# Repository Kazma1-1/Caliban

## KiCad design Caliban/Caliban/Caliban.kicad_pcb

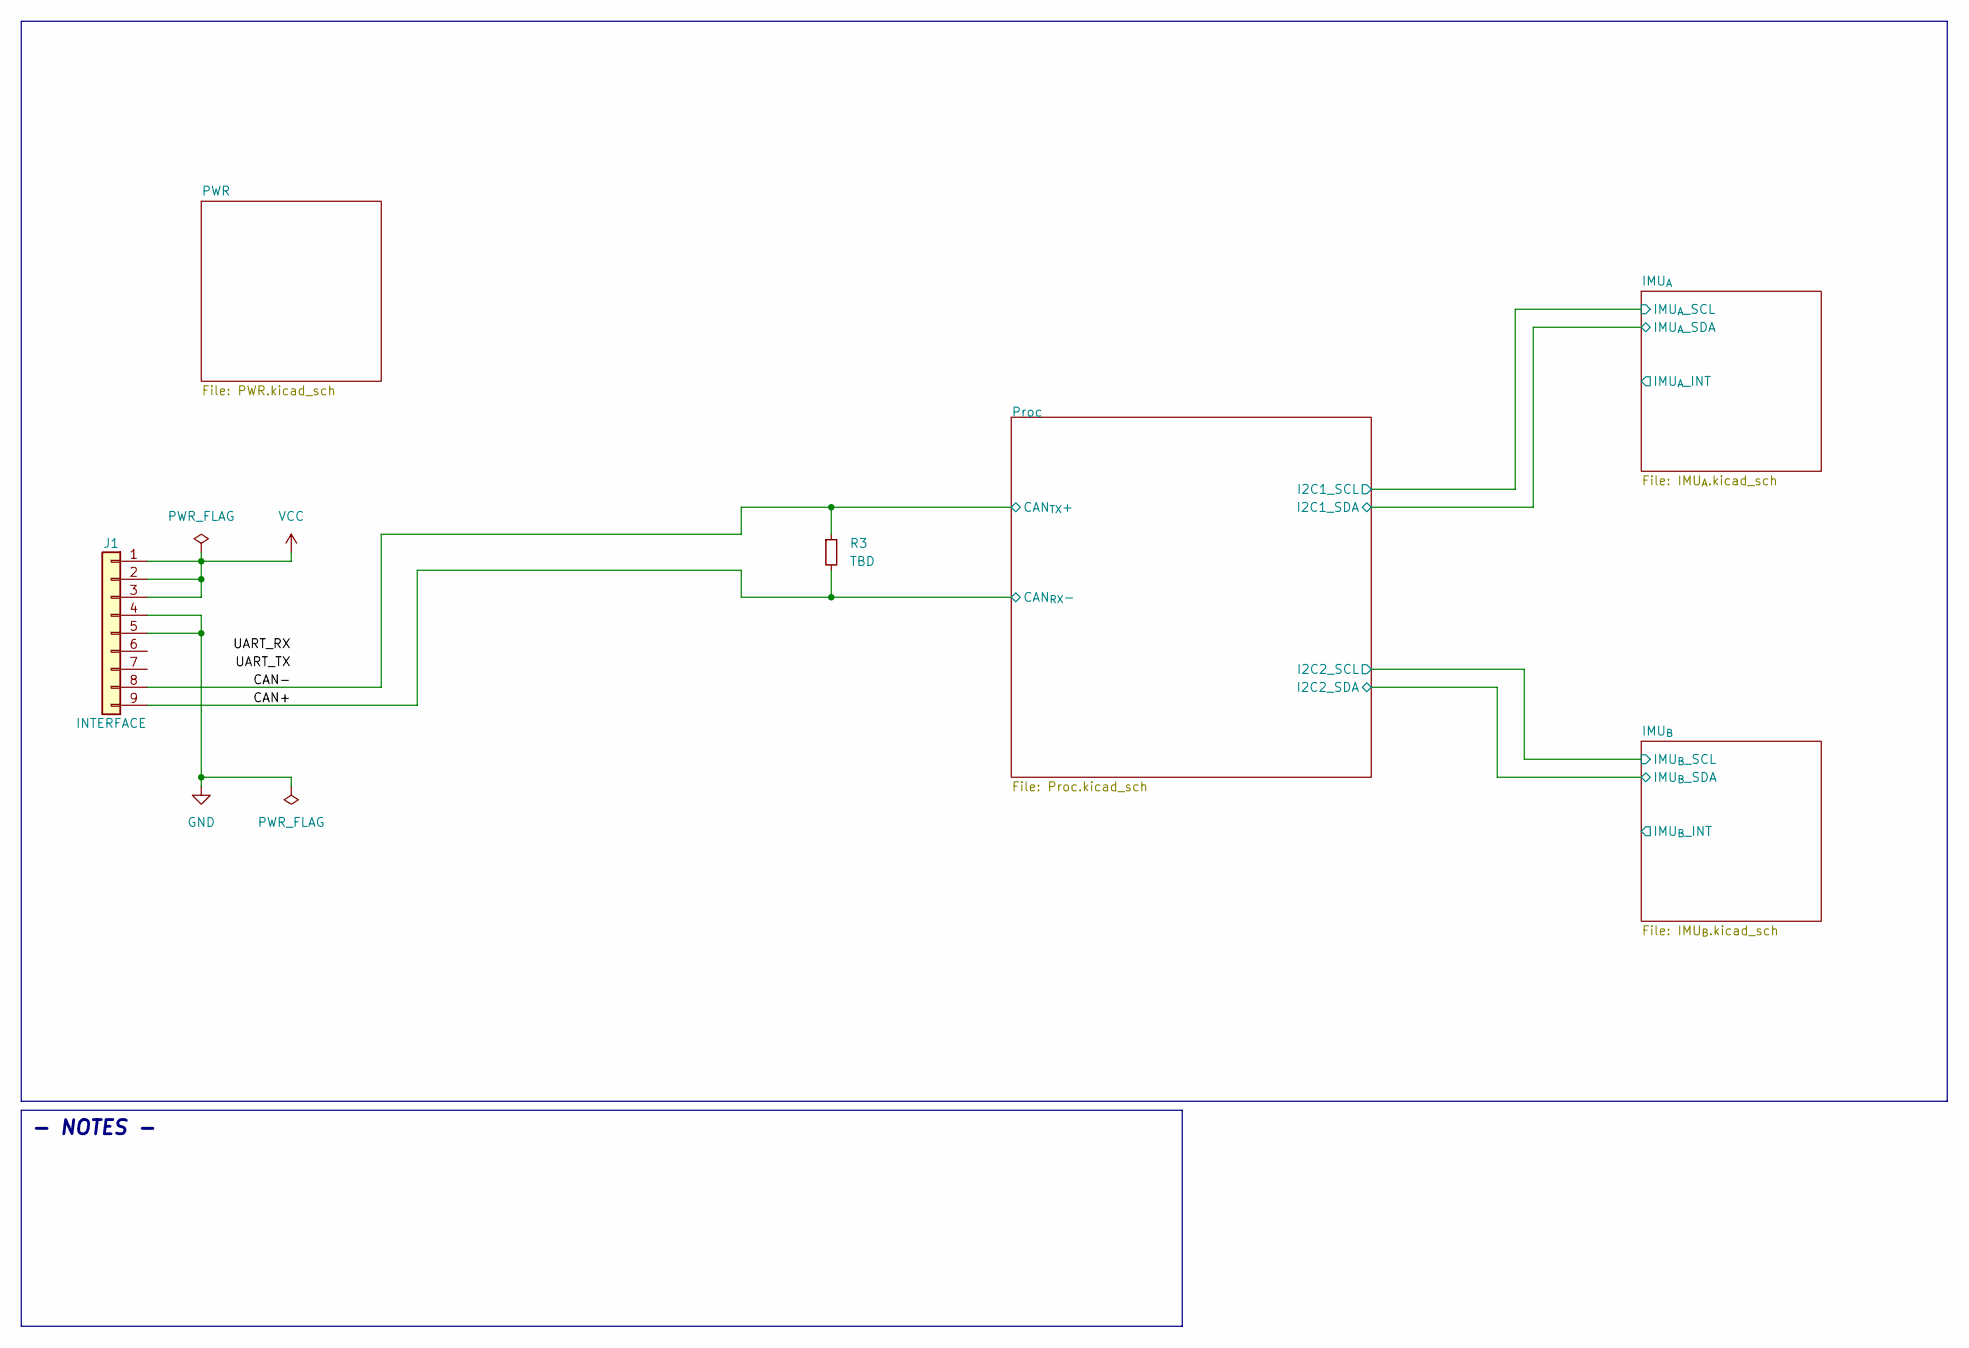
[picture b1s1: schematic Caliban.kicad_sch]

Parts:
J1: INTERFACE; DSUB-9_Female_Horizontal_P2.77x2.54mm_EdgePinOffset9.40mm
R3: TBD; R_0402_1005Metric_Pad0.72x0.64mm_HandSolder

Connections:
/CAN+: J1.9, R3.2; also elsewhere on the board
/CAN-: J1.8, R3.1; also elsewhere on the board
GND: J1.4, J1.5; also elsewhere on the board
VCC: J1.1, J1.2, J1.3; also elsewhere on the board

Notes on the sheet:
- NOTES -

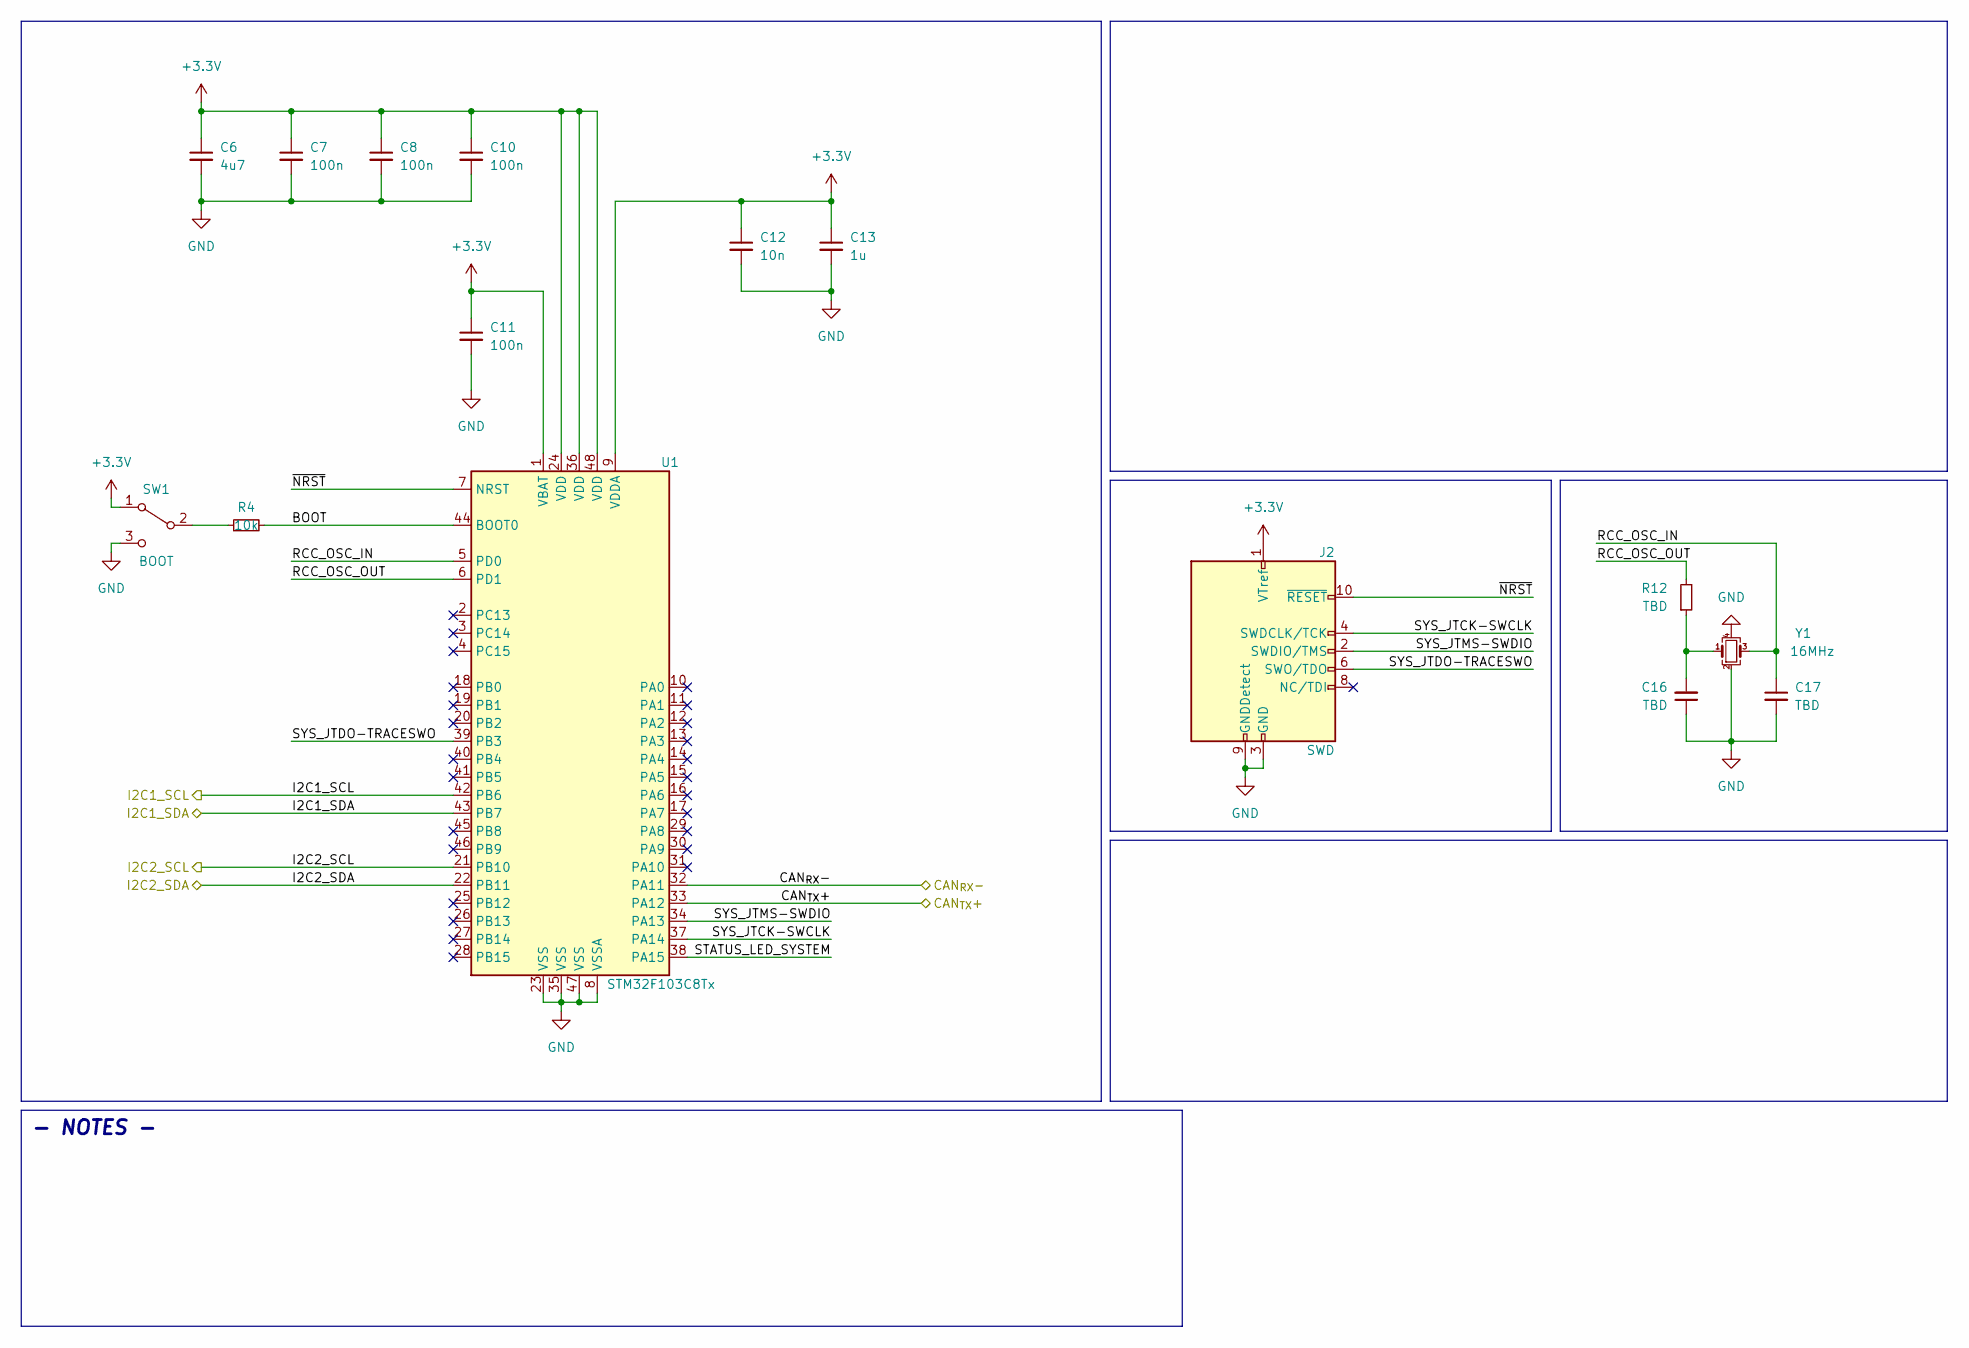
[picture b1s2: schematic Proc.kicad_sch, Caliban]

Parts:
C6: 4u7; C_0603_1608Metric_Pad1.08x0.95mm_HandSolder
C7, C8, C10, C11: 100n; C_0402_1005Metric_Pad0.74x0.62mm_HandSolder
C12: 10n; C_0402_1005Metric_Pad0.74x0.62mm_HandSolder
C13: 1u; C_0402_1005Metric_Pad0.74x0.62mm_HandSolder
C16, C17: TBD; C_0402_1005Metric_Pad0.74x0.62mm_HandSolder
J2: SWD; PinHeader_2x05_P1.27mm_Vertical_SMD
R4: 10k; R_0402_1005Metric_Pad0.72x0.64mm_HandSolder
R12: TBD; R_0402_1005Metric_Pad0.72x0.64mm_HandSolder
SW1: BOOT; SW_SPDT_PCM12
U1: STM32F103C8Tx; LQFP-48_7x7mm_P0.5mm
Y1: 16MHz; Crystal_SMD_3225-4Pin_3.2x2.5mm_HandSoldering

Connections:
+3.3V: C6.1, C7.1, C8.1, C10.1, C11.1, C12.1, C13.1, J2.1 (VTref), SW1.1 (A), U1.1 (VBAT), U1.9 (VDDA), U1.24 (VDD), U1.36 (VDD), U1.48 (VDD); also elsewhere on the board
/CAN+: U1.32 (PA11); also elsewhere on the board
/CAN-: U1.33 (PA12); also elsewhere on the board
/IMU_{A}/IMU_{A}_SCL: U1.42 (PB6); also elsewhere on the board
/IMU_{A}/IMU_{A}_SDA: U1.43 (PB7); also elsewhere on the board
/IMU_{B}/IMU_{B}_SCL: U1.21 (PB10); also elsewhere on the board
/IMU_{B}/IMU_{B}_SDA: U1.22 (PB11); also elsewhere on the board
/Proc/BOOT: R4.2, U1.44 (BOOT0)
/Proc/RCC_OSC_IN: C17.1, U1.5 (PD0), Y1.3
/Proc/RCC_OSC_OUT: R12.2, U1.6 (PD1)
/Proc/STATUS_LED_SYSTEM: U1.38 (PA15)
/Proc/SYS_JTCK-SWCLK: J2.4 (SWDCLK/TCK), U1.37 (PA14)
/Proc/SYS_JTDO-TRACESWO: J2.6 (SWO/TDO), U1.39 (PB3)
/Proc/SYS_JTMS-SWDIO: J2.2 (SWDIO/TMS), U1.34 (PA13)
/Proc/~NRST: J2.10 (~RESET), U1.7 (NRST)
GND: C6.2, C7.2, C8.2, C10.2, C11.2, C12.2, C13.2, C16.1, C17.2, J2.3 (GND), J2.5 (GND), J2.9 (GNDDetect), SW1.3 (C), U1.8 (VSSA), U1.23 (VSS), U1.35 (VSS), U1.47 (VSS), Y1.2, Y1.4; also elsewhere on the board
unnamed: C16.2, R12.1, Y1.1
unnamed: R4.1, SW1.2 (B)

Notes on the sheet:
- NOTES -

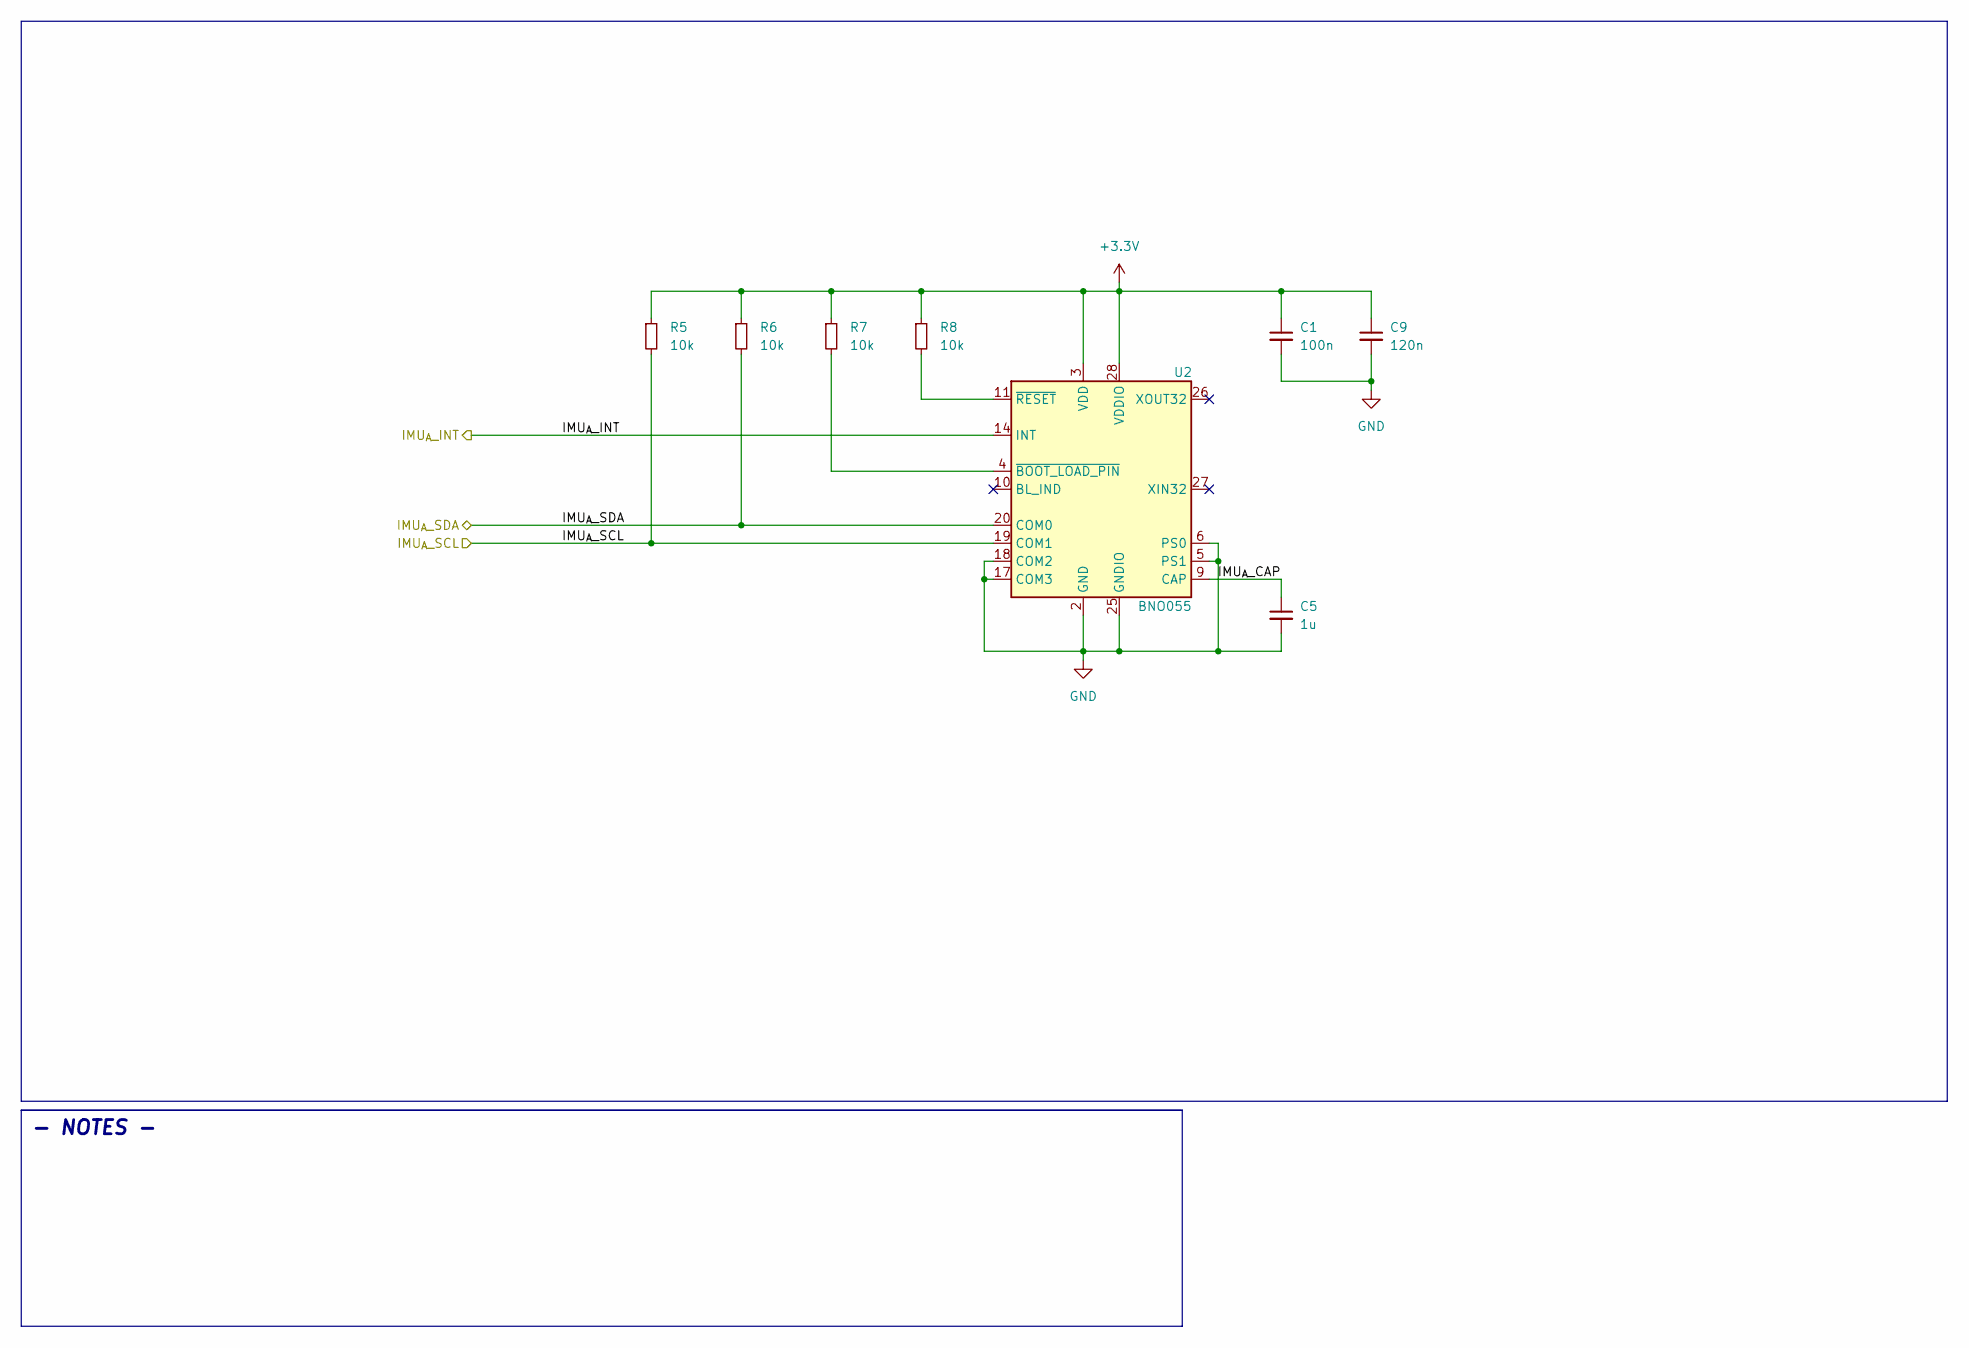
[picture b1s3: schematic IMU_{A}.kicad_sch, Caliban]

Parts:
C1: 100n; C_0402_1005Metric_Pad0.74x0.62mm_HandSolder
C5: 1u; C_0402_1005Metric_Pad0.74x0.62mm_HandSolder
C9: 120n; C_0402_1005Metric_Pad0.74x0.62mm_HandSolder
R5, R6, R7, R8: 10k; R_0402_1005Metric_Pad0.72x0.64mm_HandSolder
U2: BNO055; LGA-28_5.2x3.8mm_P0.5mm

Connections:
+3.3V: C1.1, C9.1, R5.1, R6.1, R7.1, R8.1, U2.3 (VDD), U2.28 (VDDIO); also elsewhere on the board
/IMU_{A}/IMU_{A}_CAP: C5.1, U2.9 (CAP)
/IMU_{A}/IMU_{A}_INT: U2.14 (INT)
/IMU_{A}/IMU_{A}_SCL: R5.2, U2.19 (COM1); also elsewhere on the board
/IMU_{A}/IMU_{A}_SDA: R6.2, U2.20 (COM0); also elsewhere on the board
GND: C1.2, C5.2, C9.2, U2.2 (GND), U2.5 (PS1), U2.6 (PS0), U2.15 (GNDIO), U2.16 (GNDIO), U2.17 (COM3), U2.18 (COM2), U2.25 (GNDIO); also elsewhere on the board
unnamed: R7.2, U2.4 (~BOOT_LOAD_PIN)
unnamed: R8.2, U2.11 (~RESET)

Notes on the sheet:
- NOTES -

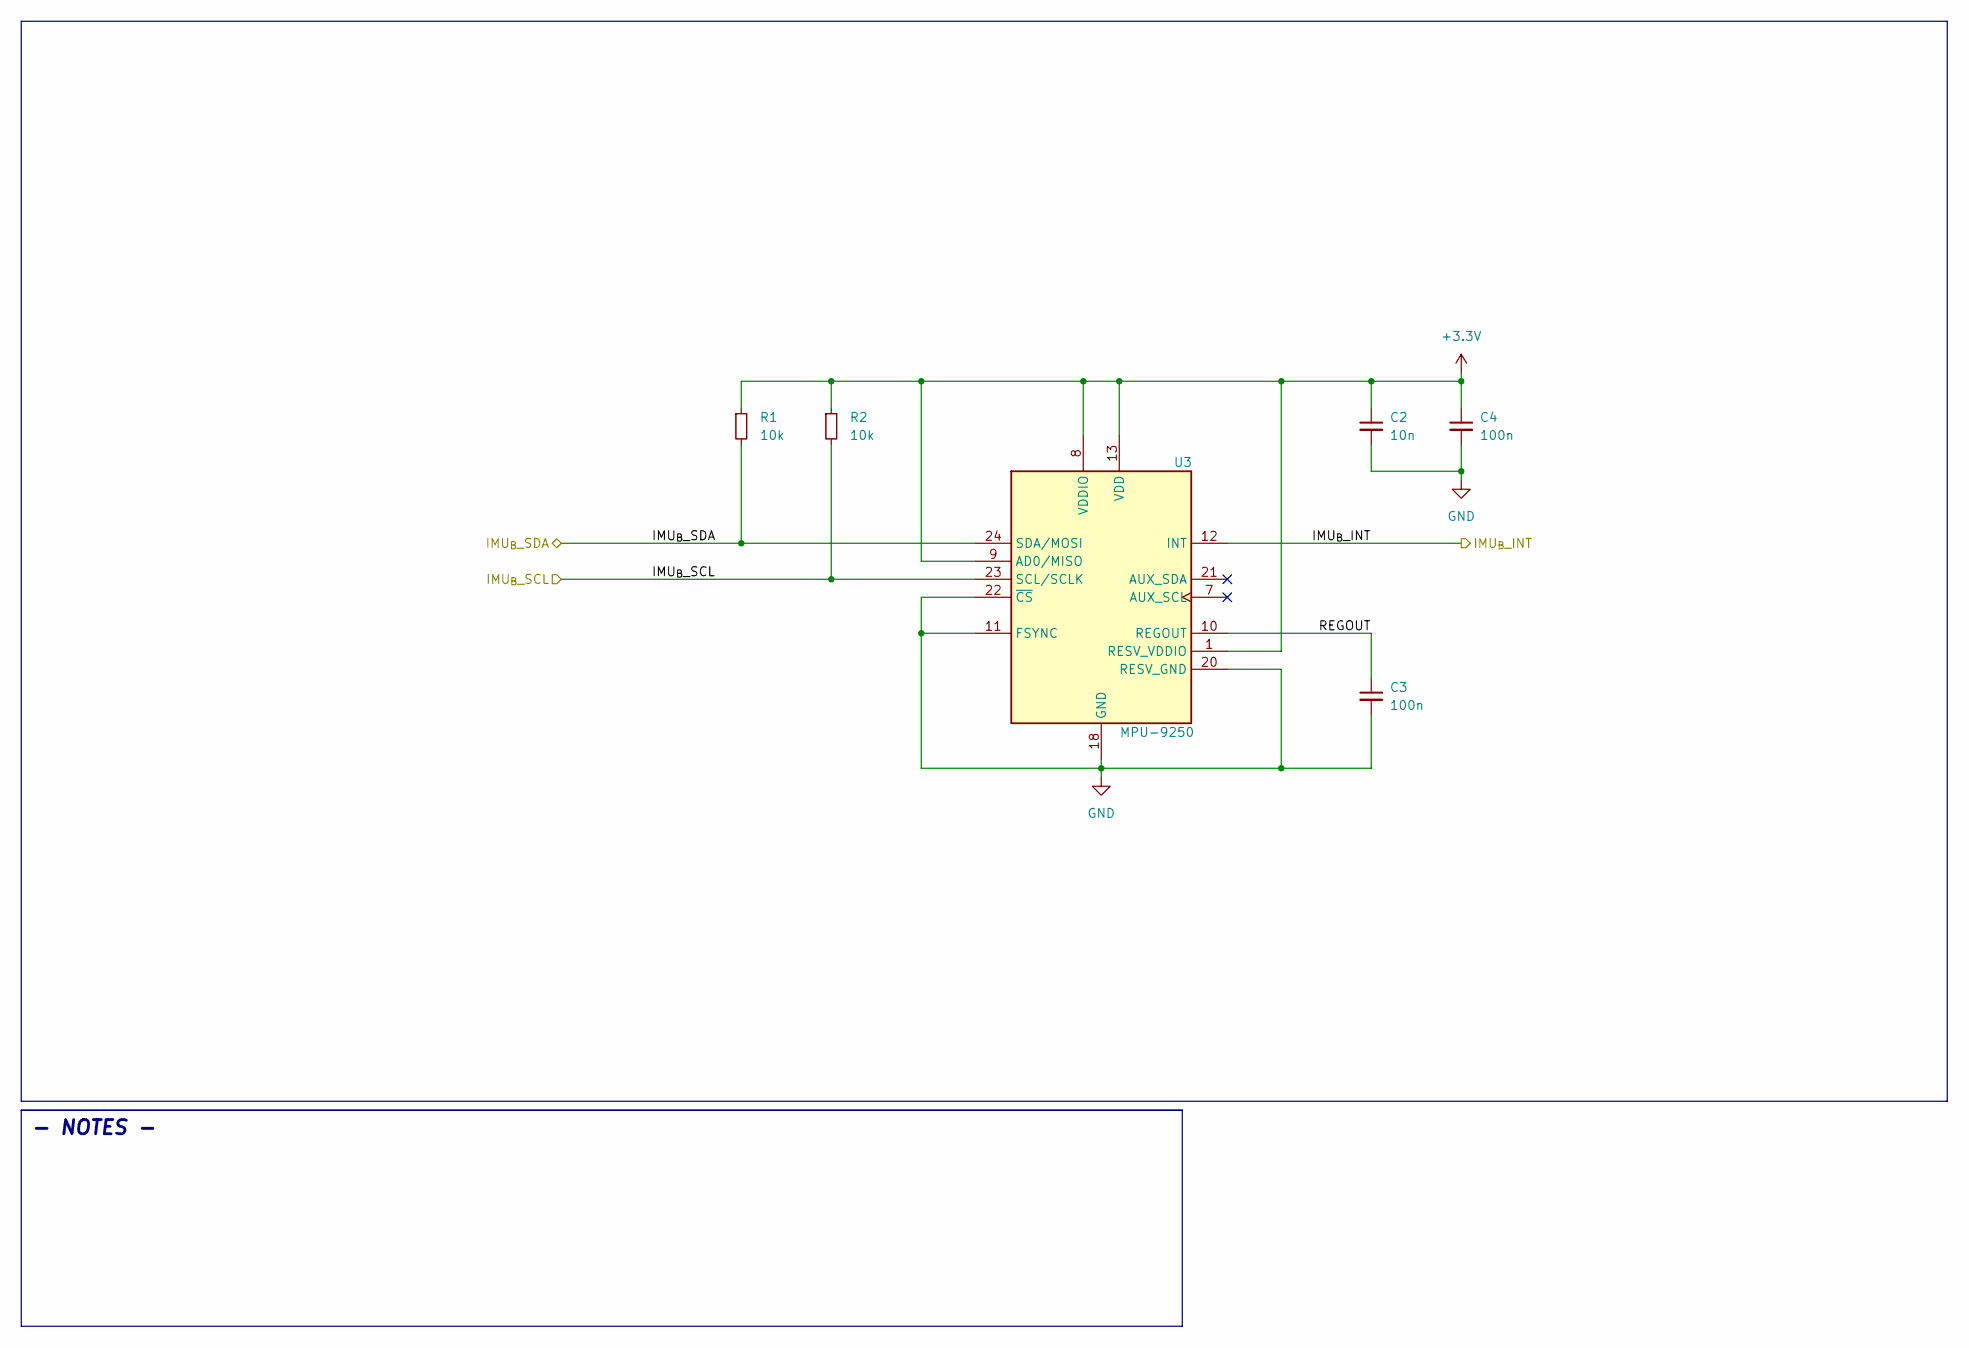
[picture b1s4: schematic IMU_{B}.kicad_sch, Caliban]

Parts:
C2: 10n; C_0402_1005Metric_Pad0.74x0.62mm_HandSolder
C3, C4: 100n; C_0402_1005Metric_Pad0.74x0.62mm_HandSolder
R1, R2: 10k; R_0402_1005Metric_Pad0.72x0.64mm_HandSolder
U3: MPU-9250; InvenSense_QFN-24_3x3mm_P0.4mm

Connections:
+3.3V: C2.1, C4.1, R1.1, R2.1, U3.1 (RESV_VDDIO), U3.8 (VDDIO), U3.9 (AD0/MISO), U3.13 (VDD); also elsewhere on the board
/IMU_{B}/IMU_{B}_INT: U3.12 (INT)
/IMU_{B}/IMU_{B}_SCL: R2.2, U3.23 (SCL/SCLK); also elsewhere on the board
/IMU_{B}/IMU_{B}_SDA: R1.2, U3.24 (SDA/MOSI); also elsewhere on the board
/IMU_{B}/REGOUT: C3.1, U3.10 (REGOUT)
GND: C2.2, C3.2, C4.2, U3.11 (FSYNC), U3.18 (GND), U3.20 (RESV_GND), U3.22 (~CS); also elsewhere on the board

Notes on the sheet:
- NOTES -

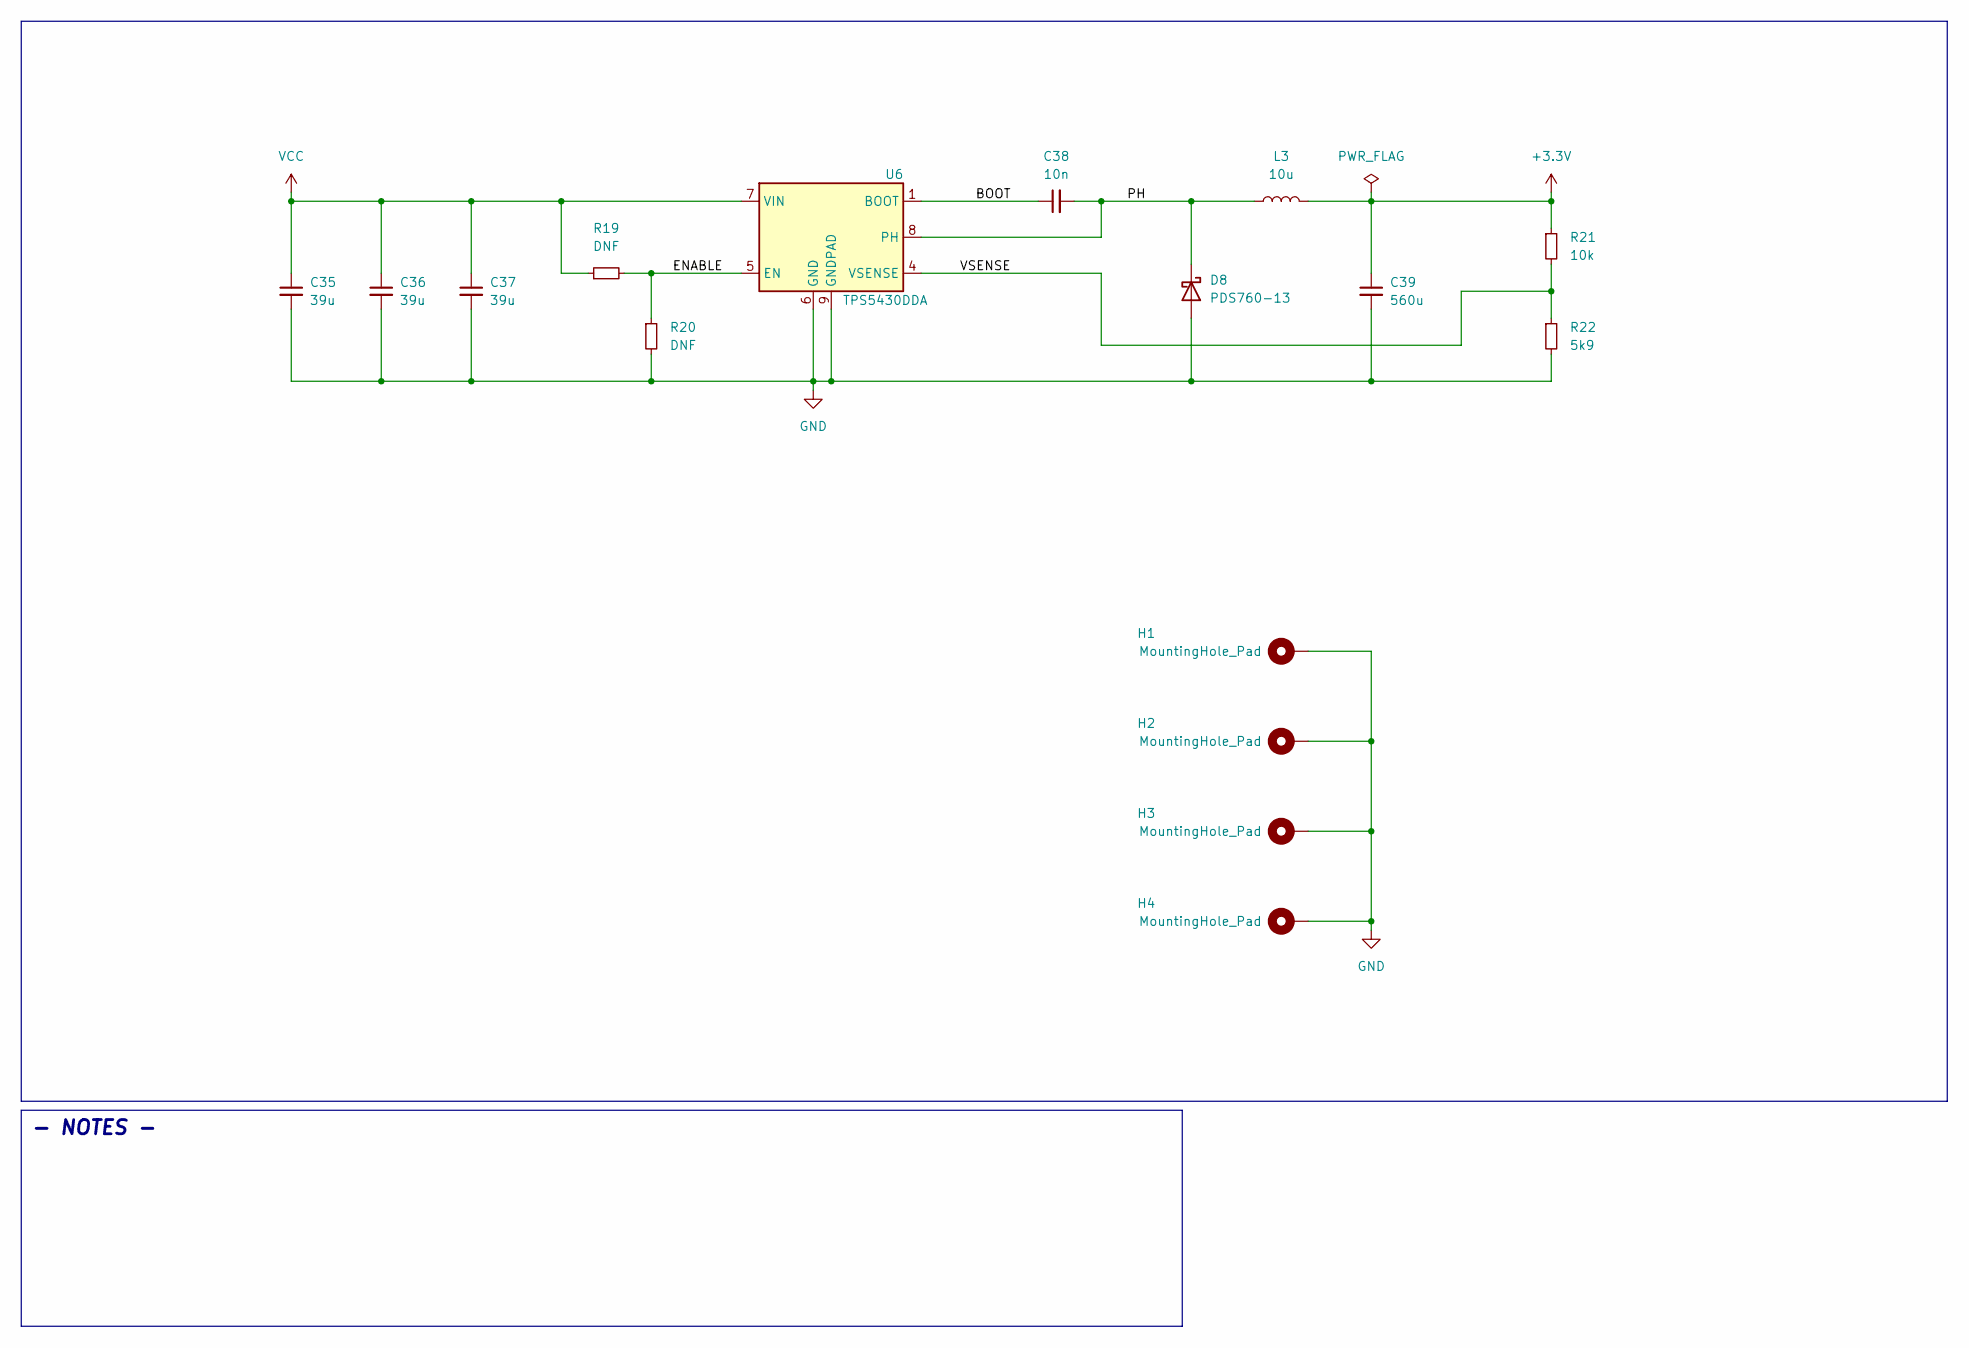
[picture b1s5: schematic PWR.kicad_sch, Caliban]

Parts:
C35, C36, C37: 39u; CP_Elec_8x11.9
C38: 10n; C_0402_1005Metric_Pad0.74x0.62mm_HandSolder
C39: 560u; CP_Elec_8x11.9
D8: PDS760-13; D_PowerDI-5
H1, H2, H3, H4: MountingHole_Pad; MountingHole_2.2mm_M2_Pad
L3: 10u; L_Vishay_IHLP-4040
R19, R20: DNF; R_0402_1005Metric_Pad0.72x0.64mm_HandSolder
R21: 10k; R_0402_1005Metric_Pad0.72x0.64mm_HandSolder
R22: 5k9; R_0402_1005Metric_Pad0.72x0.64mm_HandSolder
U6: TPS5430DDA; TI_SO-PowerPAD-8_ThermalVias

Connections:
+3.3V: C39.1, L3.2, R21.1; also elsewhere on the board
/PWR/BOOT: C38.1, U6.1 (BOOT)
/PWR/ENABLE: R19.2, R20.1, U6.5 (EN)
/PWR/PH: C38.2, D8.1 (K), L3.1, U6.8 (PH)
/PWR/VSENSE: R21.2, R22.1, U6.4 (VSENSE)
GND: C35.2, C36.2, C37.2, C39.2, D8.2 (A), H1.1, H2.1, H3.1, H4.1, R20.2, R22.2, U6.6 (GND), U6.9 (GNDPAD); also elsewhere on the board
VCC: C35.1, C36.1, C37.1, R19.1, U6.7 (VIN); also elsewhere on the board

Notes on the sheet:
- NOTES -

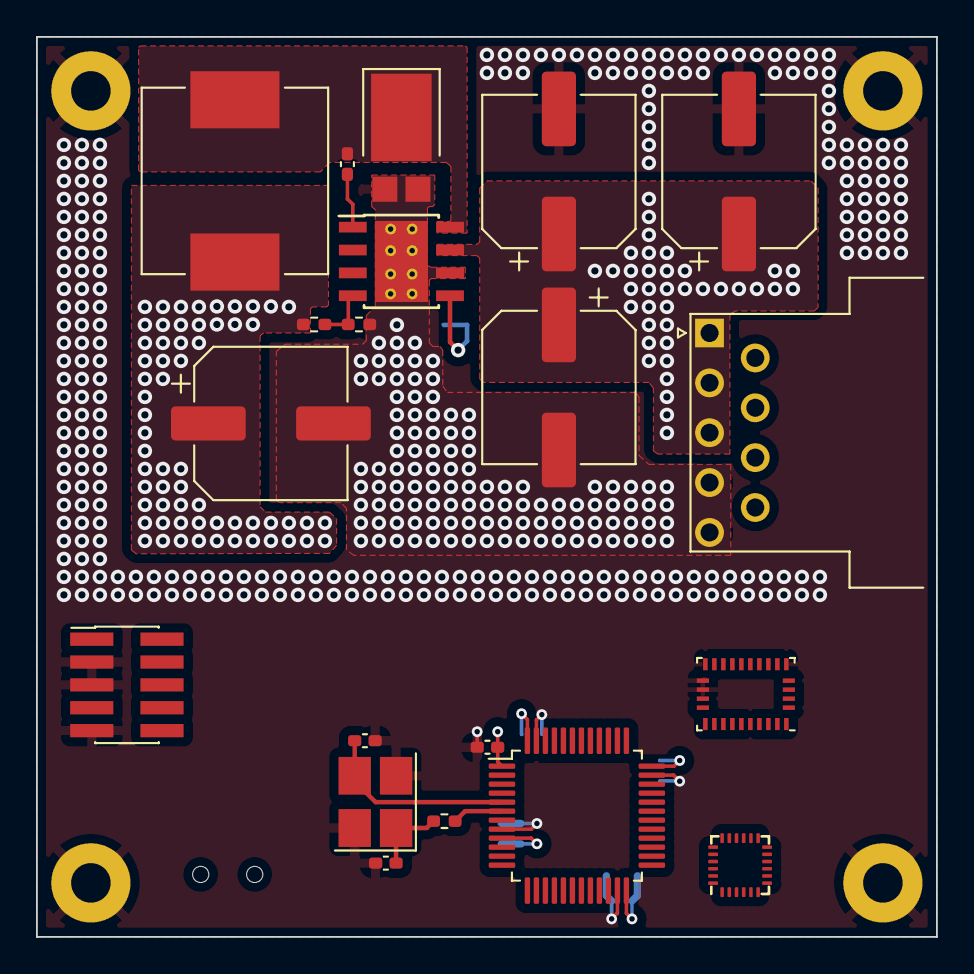
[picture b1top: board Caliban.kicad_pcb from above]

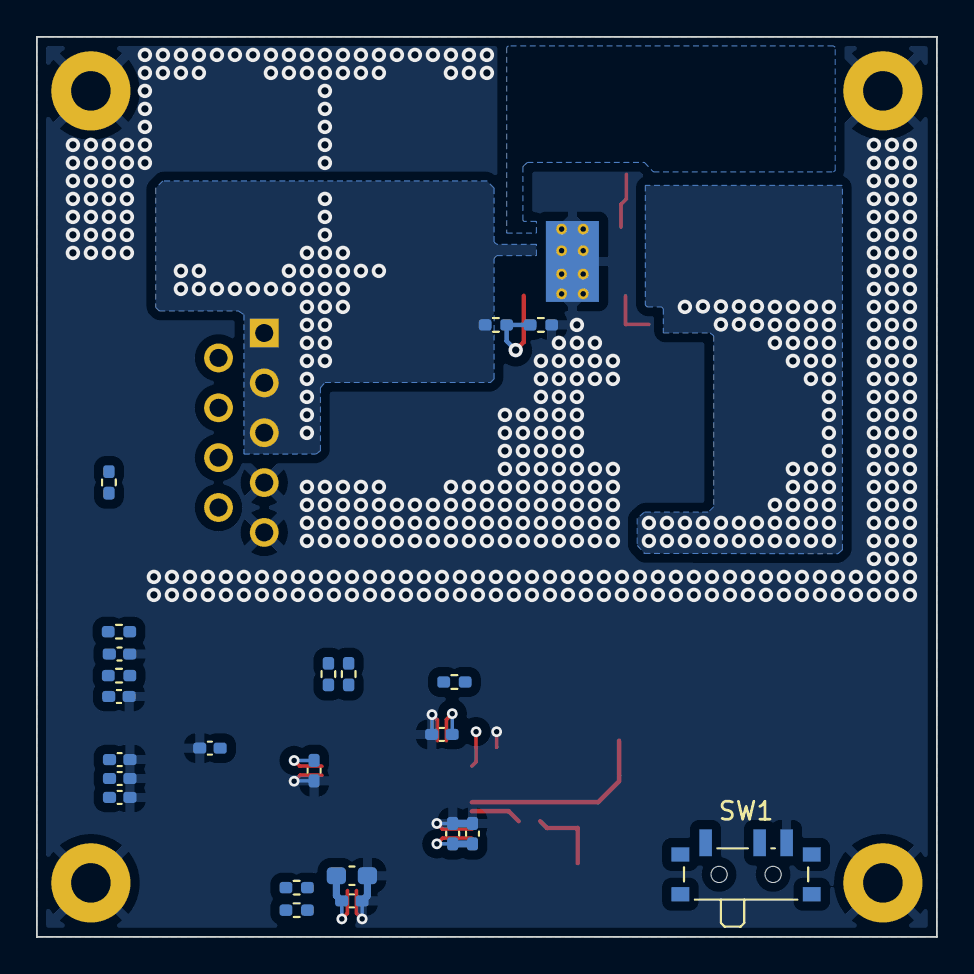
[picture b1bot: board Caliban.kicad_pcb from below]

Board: 4 copper layers, 50.0 x 50.0 mm, 47 parts (23 on the bottom side), 26 nets.

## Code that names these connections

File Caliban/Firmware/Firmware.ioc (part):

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Mcu.Name=STM32F103C(8-B)Tx
Mcu.Package=LQFP48
Mcu.UserName=STM32F103C8Tx
PA11.Mode=CAN_Activate
PA11.Signal=CAN_RX
PA12.Mode=CAN_Activate
PA12.Signal=CAN_TX
PA13.Mode=Trace_Asynchronous_SW
PA13.Signal=SYS_JTMS-SWDIO
PA14.Mode=Trace_Asynchronous_SW
PA14.Signal=SYS_JTCK-SWCLK
PB10.Mode=I2C
PB10.Signal=I2C2_SCL
PB11.Mode=I2C
PB11.Signal=I2C2_SDA
PB3.Mode=Trace_Asynchronous_SW
PB3.Signal=SYS_JTDO-TRACESWO
PB6.Mode=I2C
PB6.Signal=I2C1_SCL
PB7.Mode=I2C
PB7.Signal=I2C1_SDA
PD0-OSC_IN.Mode=HSE-External-Oscillator
PD0-OSC_IN.Signal=RCC_OSC_IN
PD1-OSC_OUT.Mode=HSE-External-Oscillator
PD1-OSC_OUT.Signal=RCC_OSC_OUT
RCC.SYSCLKFreq_VALUE=72000000
RCC.SYSCLKSource=RCC_SYSCLKSOURCE_PLLCLK
board=custom
